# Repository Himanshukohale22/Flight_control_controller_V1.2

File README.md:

# Flight_control_controller_V1.2
Hardware files for universal flight controller for small UAV's. 

### BOARD SPECIFICATION.
---

* STM32f7 cortex M4 based on board microcontroller for precision and fligt data simulation.
  * Core: Arm® 32-bit Cortex®-M7 CPU with FPU
  * Six-stage dual-issue pipeline
  • Dynamic branch prediction
  • Harvard caches (8 Kbytes of I-cache and 8 Kbytes of D-cache)
  • 64-bit AXI4 interface
  • 64-bit ITCM interface
  • 2x32-bit DTCM interfaces 
* sensors
  * MPU9250.(IMU)
    *  9-axis of freedom. (6 are used).
    * accerelometer an gyroscopic values
    * Higher calibration precision.
    * for statbility and orientation of board/vehicle.
    * configured with SPI1.
  * BMP280 .(Barometer)
    * configured with I2C .
    * barometer for altitude calculations . helps to hover the flight.
    * absolutely accurate p = 950 -- 1100 hPa.
  * NRF module
    * nrf module for communication upto 1km.
    * configured with SPI2.
  * BLE
  * WIFI
  * Servo motors
  * GPS support
  * Perhipherals
    * UART X2
    * I2C  X1
    * SPI  X1
    * CAN  X1
  * Power 
    * 3V3 sensor support
    * 5V support
    * usbB mini for testing testing.
    * jst connector i/p from 12v to 27v .
  * OSD (On screen display)
  * SD card support
  * for programme the ,board include four pins ckl , io , pwr , gnd as in 1.27mm pins(SWD). use ST-LINK.

Top Layer
---

Bottom Layer 
---

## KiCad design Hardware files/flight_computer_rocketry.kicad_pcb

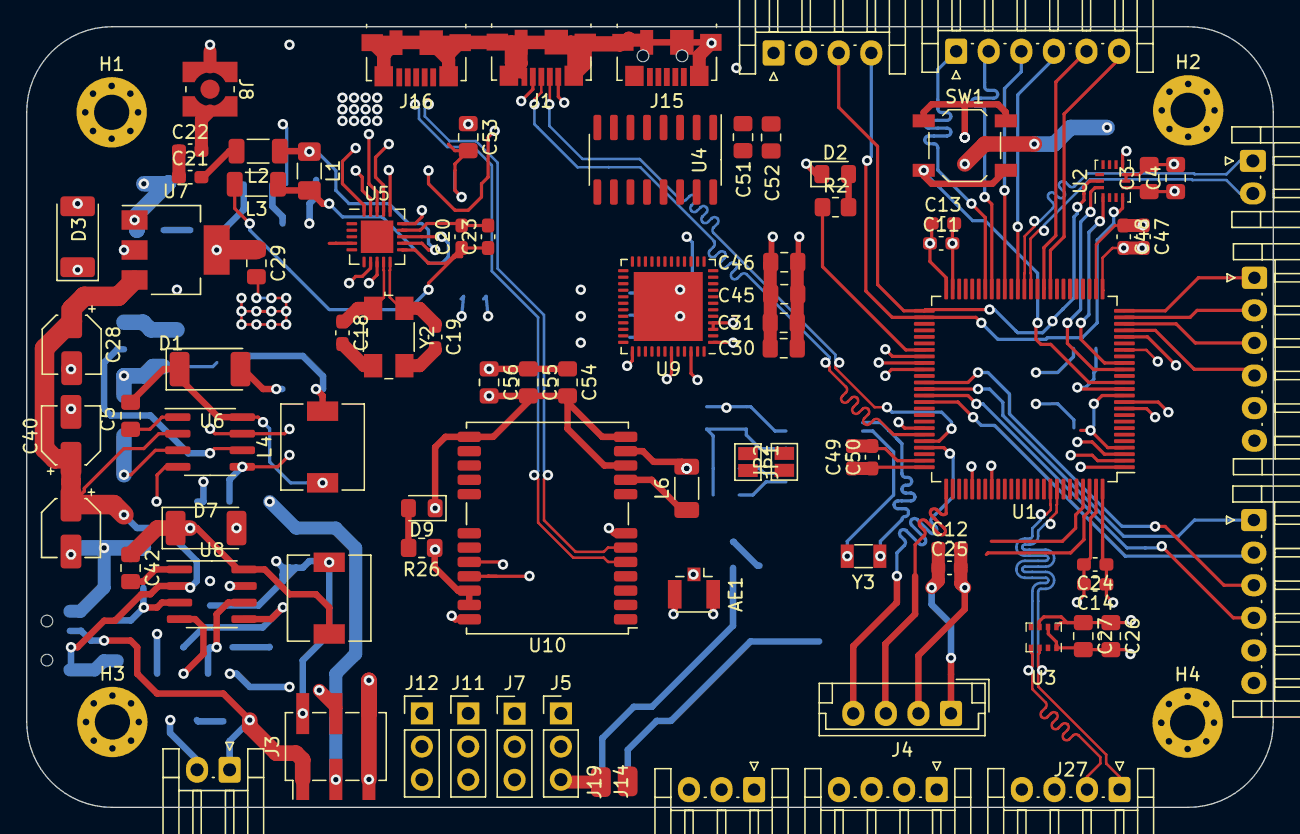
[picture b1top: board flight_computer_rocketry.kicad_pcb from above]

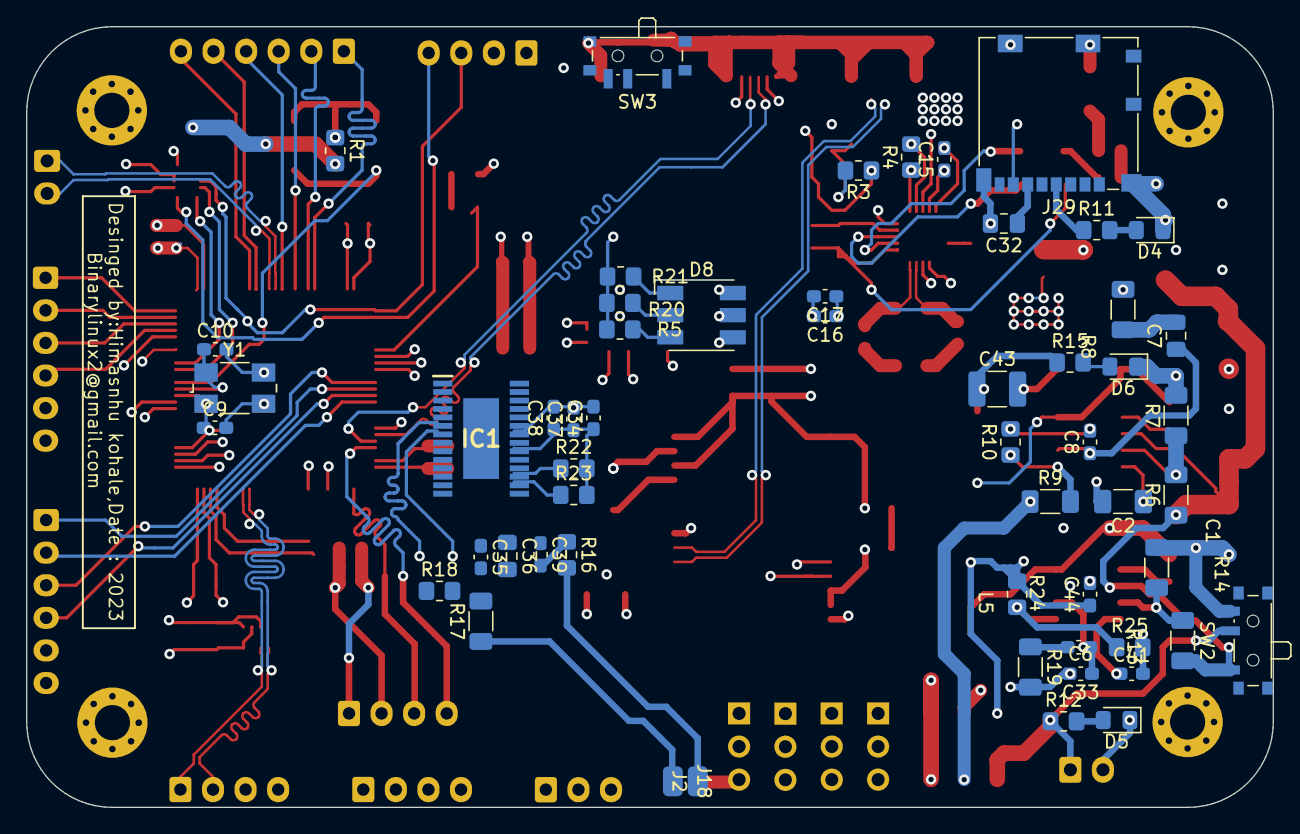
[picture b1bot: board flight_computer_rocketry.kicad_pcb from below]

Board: 4 copper layers, 95.6 x 59.9 mm, 145 parts (55 on the bottom side), 109 nets.

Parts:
AE1: Antenna_Chip; U.FL_Hirose_U.FL-R-SMT-1_Vertical
C1, C28, C40: 10uf; CP_Elec_4x3
C2: 8.2uf; C_1206_3216Metric_Pad1.33x1.80mm_HandSolder
C3, C4, C5, C26, C27, C30, C31, C32, C42, C45, C46, C51, C52, C53, C54, C55, C56: 100nf; C_0805_2012Metric_Pad1.18x1.45mm_HandSolder
C6: 10pf; C_0603_1608Metric_Pad1.08x0.95mm_HandSolder
C7: 1.8nf; C_0805_2012Metric_Pad1.18x1.45mm_HandSolder
C8: 68pf; C_0603_1608Metric_Pad1.08x0.95mm_HandSolder
C9, C10, C18, C19: 12pf; C_0603_1608Metric_Pad1.08x0.95mm_HandSolder
C11, C12, C13, C14, C24, C25, C44, C47, C48, C49, C50: 100pf; C_0603_1608Metric_Pad1.08x0.95mm_HandSolder
C15: 3.3nf; C_0603_1608Metric_Pad1.08x0.95mm_HandSolder
C16: 10nf; C_0603_1608Metric_Pad1.08x0.95mm_HandSolder
C17, C33: 1nf; C_0603_1608Metric_Pad1.08x0.95mm_HandSolder
C20: 22nf; C_0603_1608Metric_Pad1.08x0.95mm_HandSolder
C21: 1.5pf; C_0603_1608Metric_Pad1.08x0.95mm_HandSolder
C22: 1pf; C_0603_1608Metric_Pad1.08x0.95mm_HandSolder
C23: 4.7pf; C_0603_1608Metric_Pad1.08x0.95mm_HandSolder
C29, C36: 0.1uf; C_0805_2012Metric_Pad1.18x1.45mm_HandSolder
C34, C37, C38, C39: 0.1uf; C_0603_1608Metric_Pad1.08x0.95mm_HandSolder
C35: 22pf; C_0603_1608Metric_Pad1.08x0.95mm_HandSolder
C41: 8.2nf; C_0603_1608Metric_Pad1.08x0.95mm_HandSolder
C43: 47uf; C_1210_3225Metric_Pad1.33x2.70mm_HandSolder
D1, D3, D7: D_Zener; D_2010_5025Metric_Pad1.52x2.65mm_HandSolder
D2, D4, D5, D6, D9: blue; LED_0805_2012Metric_Pad1.15x1.40mm_HandSolder
D8: LED_RGB; LED_RGB_5050-6
H1, H2, H3, H4: MountingHole_Pad; MountingHole_2.7mm_M2.5_Pad_Via
IC1: AT7456E; SOP65P640X120-29N
J1, J15, J16: USB_B_Mini; USB_Micro-B_Molex_47346-0001
J2, J14, J18, J19: Conn_01x01_Pin; 1-PIN
J3: Conn_01x06_Pin; PinHeader_2x03_P2.54mm_Vertical_SMD
J4: Conn_01x04_Pin; JST_EH_B4B-EH-A_1x04_P2.50mm_Vertical
J5, J7, J11, J12: Conn_01x03_Pin; PinHeader_1x03_P2.54mm_Vertical
J6: Conn_01x03_Pin; JST_EH_S3B-EH_1x03_P2.50mm_Horizontal
J8: Conn_Coaxial; WR-MMCX_Wuerth_66012102111404_Vertical
J9, J27, J28: Conn_01x04_Pin; JST_EH_S4B-EH_1x04_P2.50mm_Horizontal
J10, J31, J32: Conn_01x06_Pin; JST_EH_S6B-EH_1x06_P2.50mm_Horizontal
J13, J17: Conn_01x02_Male; JST_EH_S2B-EH_1x02_P2.50mm_Horizontal
J29: Micro_SD_Card_Det2; microSD_HC_Molex_104031-0811
JP1, JP2: Jumper_2_Bridged; SolderJumper-2_P1.3mm_Open_Pad1.0x1.5mm
L1: 8.2nH; L_1206_3216Metric_Pad1.42x1.75mm_HandSolder
L2: 3.5nH; L_1206_3216Metric_Pad1.22x1.90mm_HandSolder
L3: 2.7nH; L_1206_3216Metric_Pad1.22x1.90mm_HandSolder
L4: 22uH; L_6.3x6.3_H3
L5: 29nH; L_6.3x6.3_H3
L6: 47nH; L_1206_3216Metric_Pad1.22x1.90mm_HandSolder
R1, R2, R5, R11, R12, R15, R20, R21, R25, R26: 1k; R_0805_2012Metric_Pad1.20x1.40mm_HandSolder
R3: 10K; R_0805_2012Metric_Pad1.20x1.40mm_HandSolder
R4: 22k; R_0805_2012Metric_Pad1.20x1.40mm_HandSolder
R6, R13: 169K; R_1206_3216Metric_Pad1.30x1.75mm_HandSolder
R7, R14: 13.3K; R_1206_3216Metric_Pad1.30x1.75mm_HandSolder
R8, R19: 48K; R_1206_3216Metric_Pad1.30x1.75mm_HandSolder
R9: 10k; R_1206_3216Metric_Pad1.30x1.75mm_HandSolder
R10: 1.96K; R_0805_2012Metric_Pad1.20x1.40mm_HandSolder
R16: 75R; R_0805_2012Metric_Pad1.20x1.40mm_HandSolder
R17: 150R; R_1206_3216Metric_Pad1.30x1.75mm_HandSolder
R18, R22, R23: 1K; R_0805_2012Metric_Pad1.20x1.40mm_HandSolder
R24: 8.2k; R_0805_2012Metric_Pad1.20x1.40mm_HandSolder
SW1: SW_Push_Dual_x2; SW_SPST_TL3342
SW2, SW3: SW_SPDT; SW_SPDT_PCM12
U1: STM32F722VCTx; LQFP-100_14x14mm_P0.5mm
U2: BMI160; Bosch_LGA-14_3x2.5mm_P0.5mm
U3: BMP280; Bosch_LGA-8_2x2.5mm_P0.65mm_ClockwisePinNumbering
U4: CH340G; SOIC-16_3.9x9.9mm_P1.27mm
U5: NRF24L01; QFN-20-1EP_4x4mm_P0.5mm_EP2.5x2.5mm
U6, U8: TPS54233; SOIC-8_3.9x4.9mm_P1.27mm
U7: AMS1117-3.3; SOT-223-3_TabPin2
U9: ESP32-PICO-D4; QFN-48-1EP_7x7mm_P0.5mm_EP5.3x5.3mm
U10: NEO-8Q; ublox_NEO
Y1: Crystal_GND23_Small; Crystal_SMD_0603-4Pin_6.0x3.5mm
Y2: Crystal_GND23; Crystal_SMD_0603-4Pin_6.0x3.5mm
Y3: Crystal; Crystal_SMD_3215-2Pin_3.2x1.5mm

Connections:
3V3: C3.1, C4.1, C11.1, C12.1, C13.1, C14.1, C16.1, C17.1, C24.1, C25.1, C26.1, C27.1, C30.1, C31.1, C45.1, C46.1, C47.1, C48.1, C49.1, C50.1, C51.1, C52.1, C53.2, C54.1, C55.1, C56.1, J3.4, J4.1, J9.3, J16.1 (VBUS), J27.3, J29.4 (VDD), R3.2, R11.1, R26.1, U1.6 (VBAT), U1.11 (VDD), U1.21 (VDDA), U1.27 (VDD), U1.50 (VDD), U1.75 (VDD), U1.100 (VDD), U2.5 (VDDIO), U2.8 (VDD), U3.6 (VDDIO), U3.8 (VDD), U4.4 (V3), U4.16 (VCC), U5.7 (VDD), U5.15 (VDD), U5.18 (VDD), U9.1 (VDDA), U9.3 (VDDA3P3), U9.4 (VDDA3P3), U9.19 (VDD3P3_RTC), U9.37 (VDD3P3_CPU), U9.43 (VDDA), U9.46 (VDDA), U10.7 (VDD_USB), U10.22 (V_BCKP), U10.23 (VCC)
5V: C34.1, C37.1, C38.1, C43.1, IC1.3 (DVDD), IC1.19 (~RESET), IC1.21 (AVDD), IC1.24 (PVDD), J3.3, J6.2, J31.5, J32.5, L4.2, R9.1, R15.1, R18.2, R22.2, R23.2
9V: C44.1, J3.2, J5.2, J7.2, J11.2, J12.2, L5.2, R24.1
+3.3V: C29.1, D3.1 (K), U7.2 (VO)
AGND: AE1.2 (PCB_Trace), C1.2, C2.2, C3.2, C4.2, C8.2, C9.2, C10.2, C11.2, C12.2, C13.2, C14.2, C15.2, C16.2, C17.2, C18.2, C19.2, C20.2, C22.2, C23.2, C24.2, C25.2, C26.2, C27.2, C28.2, C29.2, C30.2, C31.2, C32.2, C33.2, C34.2, C37.2, C38.2, C40.2, C41.2, C43.2, C44.2, C45.2, C46.2, C47.2, C48.2, C49.2, C50.2, C51.2, C52.2, C53.1, C54.2, C55.2, C56.2, D1.2 (A), D2.1 (K), D3.2 (A), D4.1 (K), D5.1 (K), D6.1 (K), D7.2 (A), D9.1 (K), H1.1, H2.1, H3.1, H4.1, IC1.4 (DGND), IC1.20 (AGND), IC1.23 (PGND), J1.5 (GND), J1.6 (Shield), J3.5, J3.6, J4.2, J5.3, J6.3, J7.3, J8.2 (Ext), J9.4, J11.3, J12.3, J15.5 (GND), J15.6 (Shield), J16.5 (GND), J16.6 (Shield), J17.2, J19.1, J27.4, J29.7 (DAT0), J29.11 (SHIELD), J31.6, J32.6, R1.2, R4.2, R5.2, R7.2, R8.2, R10.2, R14.2, R19.2, R20.2, R21.2, R25.2, SW2.3 (C), SW3.1 (A), U1.10 (VSS), U1.19 (VSSA), U1.26 (VSS), U1.49 (VSS), U1.74 (VSS), U1.99 (VSS), U2.6 (GNDIO), U2.7 (GND), U3.1 (GND), U3.7 (GND), U4.1 (GND), U5.8 (VSS), U5.14 (VSS), U5.17 (VSS), U5.20 (VSS), U6.7 (GND), U7.1 (GND), U8.7 (GND), U9.49 (GND), U10.10 (GND), U10.12 (GND), U10.13 (GND), U10.24 (GND), Y1.2, Y1.3, Y2.2, Y2.3
COMP: C7.1, C8.1, U6.6 (COMP)
COMP_9V: C6.1, C33.1, U8.6 (COMP)
CONTROL_LED: R2.1, U1.57 (PD10)
CS_SPI1: IC1.8 (~CS), J29.2 (DAT3/CD), U1.28 (PA4), U5.2 (CSN)
CS_SPI2: J28.4, U1.52 (PB13), U2.4 (INT1)
D+: J15.3 (D+), U4.5 (UD+)
D-: J15.2 (D-), U4.6 (UD-)
HS: IC1.18 (~HSYNC), R22.1
I2C1+: J27.2, U1.92 (PB6), U3.4 (SCK)
I2C1-: J27.1, U1.93 (PB7), U3.3 (SDI)
LED_BLUE: D8.6 (RA), U1.58 (PD11)
LED_GREEN: D8.5 (GA), U1.59 (PD12)
LED_RED: D8.4 (BA), U1.60 (PD13)
LOS: IC1.12 (LOS), R18.1
M1: J31.4, U1.22 (PA0)
M2: J31.3, U1.23 (PA1)
M3: J31.2, U1.24 (PA2)
M4: J31.1, U1.25 (PA3)
M5: J32.4, U1.64 (PC7)
M6: J32.1, U1.63 (PC6)
M7: J32.2, U1.65 (PC8)
M8: J32.3, U1.62 (PD15)
MISO_SPI1: IC1.11 (SDOUT), J29.3 (CMD), U1.30 (PA6), U5.5 (MISO)
MISO_SPI2: J28.1, U1.17 (PC2), U2.1 (SDO)
MOSI_SPI1: IC1.9 (SDIN), J29.8 (DAT1), U1.31 (PA7), U5.4 (MOSI)
MOSI_SPI2: J28.2, U1.16 (PC1), U2.14 (SDx)
unnamed: C6.2, R19.1
unnamed: C7.2, R8.1
unnamed: C21.2, L2.2
unnamed: C35.2, C36.2, R17.2
unnamed: C39.2, R16.1
unnamed: C5.1, D1.1 (K), L4.1, U6.8 (PH)
unnamed: D2.2 (A), R2.2
unnamed: D4.2 (A), R11.2
unnamed: D5.2 (A), R12.2
unnamed: D6.2 (A), R15.2
unnamed: C42.1, D7.1 (K), L5.1, U8.8 (PH)
unnamed: D8.3 (BK), R5.1
unnamed: D8.2 (GK), R20.1
unnamed: D8.1 (RK), R21.1
unnamed: D9.2 (A), R26.2
unnamed: IC1.5 (CLKIN), Y3.2
unnamed: C35.1, IC1.25 (SAG)
unnamed: C39.1, IC1.22 (VIN)
unnamed: C36.1, IC1.26 (VOUT)
unnamed: IC1.6 (XFB), Y3.1
unnamed: J2.1, R17.1
unnamed: C21.1, C22.1, J8.1 (In)
unnamed: J18.1, R16.2
unnamed: C32.1, J29.6 (VSS)
unnamed: R1.1, SW1.1 (C)
unnamed: SW1.2 (D), U1.14 (NRST)
unnamed: SW3.2 (B), U1.94 (BOOT0)
unnamed: R3.1, SW3.3 (C)
unnamed: C9.1, U1.12 (PH0), Y1.1
unnamed: C10.1, U1.13 (PH1), Y1.4
unnamed: L1.1, L2.1, U5.12 (ANT1)
unnamed: L1.2, L3.1, U5.13 (ANT2)
unnamed: C15.1, U5.19 (DVDD)
unnamed: R4.1, U5.16 (IREF)
unnamed: C20.1, C23.1, L3.2, U5.11 (VDD_PA)
unnamed: C5.2, U6.1 (BOOT)
unnamed: R6.2, R7.1, U6.3 (EN)
unnamed: R9.2, R10.1, U6.5 (FB)
unnamed: C2.1, U6.4 (SS)
unnamed: C42.2, U8.1 (BOOT)
unnamed: R13.2, R14.1, U8.3 (EN)
unnamed: R24.2, R25.1, U8.5 (FB)
unnamed: C41.1, U8.4 (SS)
PPM_CAM: J6.1, U1.53 (PB14)
PWM1: J10.6, U1.34 (PB0)
PWM2: J10.5, U1.35 (PB1)
PWM3: J10.4, U1.39 (PE9)
PWM4: J10.3, U1.41 (PE11)
PWM5: J10.2, U1.43 (PE13)
PWM6: J10.1, U1.44 (PE14)
RF_IN: AE1.1 (FEED), L6.2, U10.11 (RF_IN)
RXDP_ESP: JP1.1 (A), U4.3 (RXD), U9.40 (U0RXD/IO3)
RXDP_ESP_TO_STM32: JP2.2 (B), U1.97 (PE0)
SCK_SPI1: IC1.10 (SCLK), J29.5 (CLK), U1.29 (PA5), U5.3 (SCK)
SCK_SPI2: J28.3, U1.51 (PB12), U2.13 (SCx)
SERVO_1: J5.1, U1.1 (PE2)
SERVO_2: J7.1, U1.2 (PE3)
SERVO_3: J11.1, U1.3 (PE4)
SERVO_4: J12.1, U1.4 (PE5)
SYS_JTCK_SWCLK: J4.3, U1.76 (PA14)
SYS_JTMS_SWDIO: J4.4, U1.72 (PA13)
TXDP_ESP: JP2.1 (A), U4.2 (TXD), U9.41 (U0TXD/IO1)
TXDP_ESP_TO_STM32: JP1.2 (B), U1.98 (PE1)
UART5_RX: J9.2, U1.83 (PD2), U10.20 (TXD/SPI_MISO)
UART5_TX: J9.1, U1.80 (PC12), U10.21 (RXD/SPI_MOSI)
UART7+: J13.2, U1.37 (PE7)
UART7-: J13.1, U1.38 (PE8)
USB_+: J1.3 (D+), U1.70 (PA11)
USB_-: J1.2 (D-), U1.71 (PA12)
USB_GPS+: J16.3 (D+), U10.5 (USB_DM)
USB_GPS-: J16.2 (D-), U10.6 (USB_DP)
USB_ID: J1.4 (ID), U1.69 (PA10)
VCC_RF: L6.1, U10.9 (VCC_RF)
VIN: J1.1 (VBUS), J3.1, J17.1, R12.1, SW2.2 (B)
VIN_TO_PARA: C1.1, C28.1, C40.1, R6.1, R13.1, SW2.1 (A), U6.2 (VIN), U7.3 (VI), U8.2 (VIN)
VS: IC1.17 (~VSYNC), R23.1
cr+: C18.1, U5.9 (XC2), Y2.1
cr-: C19.1, U5.10 (XC1), Y2.4

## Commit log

2024-04-04 Create kicad_files
